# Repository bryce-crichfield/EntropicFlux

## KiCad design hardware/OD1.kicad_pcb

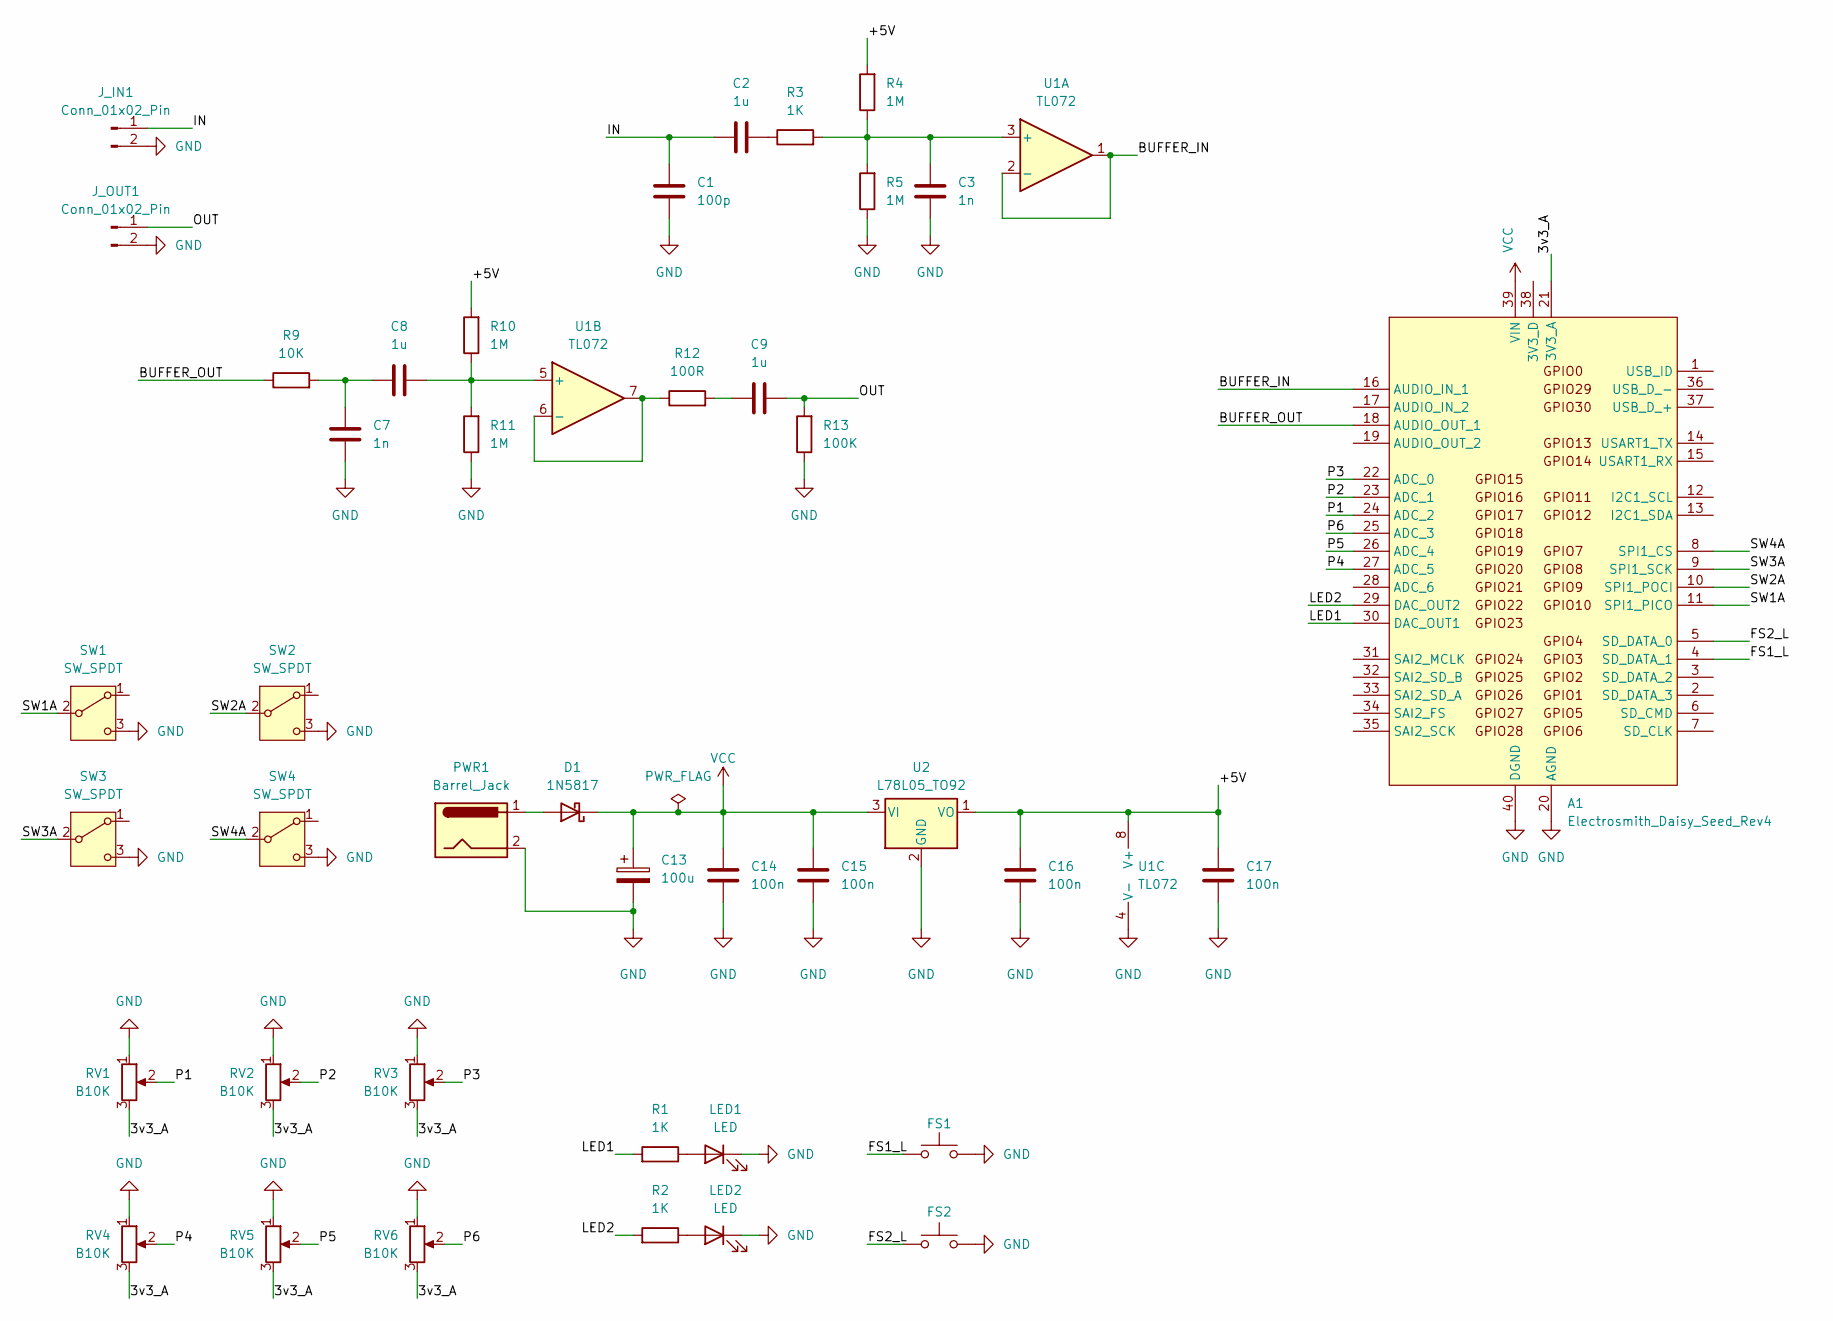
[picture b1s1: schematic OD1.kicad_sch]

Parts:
A1: Electrosmith_Daisy_Seed_Rev4; Electrosmith_Daisy_Seed
C1: 100p; C_Rect_L7.2mm_W2.5mm_P5.00mm_FKS2_FKP2_MKS2_MKP2
C2, C8, C9: 1u; C_Rect_L7.2mm_W2.5mm_P5.00mm_FKS2_FKP2_MKS2_MKP2
C3, C7: 1n; C_Rect_L7.2mm_W2.5mm_P5.00mm_FKS2_FKP2_MKS2_MKP2
C13: 100u; CP_Radial_D8.0mm_P3.50mm
C14, C15, C16, C17: 100n; C_Rect_L7.2mm_W2.5mm_P5.00mm_FKS2_FKP2_MKS2_MKP2
D1: 1N5817; D_DO-41_SOD81_P10.16mm_Horizontal
FS1, FS2: PinHeader_1x02_P2.54mm_Vertical
J_IN1: Conn_01x02_Pin; PinHeader_1x02_P2.54mm_Vertical
J_OUT1: Conn_01x02_Pin; PinHeader_1x02_P2.54mm_Vertical
LED1, LED2: LED; LED_D5.0mm
PWR1: Barrel_Jack; PinHeader_1x02_P2.54mm_Vertical
R1, R2, R3: 1K; R_Axial_DIN0207_L6.3mm_D2.5mm_P10.16mm_Horizontal
R4, R5, R10, R11: 1M; R_Axial_DIN0207_L6.3mm_D2.5mm_P10.16mm_Horizontal
R9: 10K; R_Axial_DIN0207_L6.3mm_D2.5mm_P10.16mm_Horizontal
R12: 100R; R_Axial_DIN0207_L6.3mm_D2.5mm_P10.16mm_Horizontal
R13: 100K; R_Axial_DIN0207_L6.3mm_D2.5mm_P10.16mm_Horizontal
RV1, RV2, RV3, RV4, RV5, RV6: B10K; Potentiometer_3Pin_Holes
SW1, SW2, SW3, SW4: SW_SPDT; Toggle_Switch_3Pin_Holes
U1: TL072; DIP-8_W7.62mm
U2: L78L05_TO92; TO-92_Inline

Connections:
/3v3_A: A1.21 (3V3_A), RV1.3, RV2.3, RV3.3, RV4.3, RV5.3, RV6.3
/+5V: C16.2, C17.2, R4.2, R10.2, U1.8 (V+), U2.1 (VO)
/BUFFER_IN: A1.16 (AUDIO_IN_1), U1.1, U1.2 (-)
/BUFFER_OUT: A1.18 (AUDIO_OUT_1), R9.1
/FS1_L: A1.4 (SD_DATA_1), FS1.1
/FS2_L: A1.5 (SD_DATA_0), FS2.1
/IN: C1.1, C2.1, J_IN1.1
/LED1: A1.30 (DAC_OUT1), R1.2
/LED2: A1.29 (DAC_OUT2), R2.2
/OUT: C9.2, J_OUT1.1, R13.2
/P1: A1.24 (ADC_2), RV1.2
/P2: A1.23 (ADC_1), RV2.2
/P3: A1.22 (ADC_0), RV3.2
/P4: A1.27 (ADC_5), RV4.2
/P5: A1.26 (ADC_4), RV5.2
/P6: A1.25 (ADC_3), RV6.2
/SW1A: A1.11 (SPI1_PICO), SW1.2 (B)
/SW2A: A1.10 (SPI1_POCI), SW2.2 (B)
/SW3A: A1.9 (SPI1_SCK), SW3.2 (B)
/SW4A: A1.8 (SPI1_CS), SW4.2 (B)
GND: A1.20 (AGND), A1.40 (DGND), C1.2, C3.2, C7.2, C13.2, C14.1, C15.1, C16.1, C17.1, FS1.2, FS2.2, J_IN1.2, J_OUT1.2, LED1.1 (K), LED2.1 (K), PWR1.2, R5.1, R11.1, R13.1, RV1.1, RV2.1, RV3.1, RV4.1, RV5.1, RV6.1, SW1.3 (C), SW2.3 (C), SW3.3 (C), SW4.3 (C), U1.4 (V-), U2.2 (GND)
unnamed: C2.2, R3.1
unnamed: C7.1, C8.1, R9.2
unnamed: C9.1, R12.2
unnamed: D1.2 (A), PWR1.1
unnamed: LED1.2 (A), R1.1
unnamed: LED2.2 (A), R2.1
unnamed: C3.1, R3.2, R4.1, R5.2, U1.3 (+)
unnamed: C8.2, R10.1, R11.2, U1.5 (+)
unnamed: R12.1, U1.6 (-), U1.7
VCC: A1.39 (VIN), C13.1, C14.2, C15.2, D1.1 (K), U2.3 (VI)

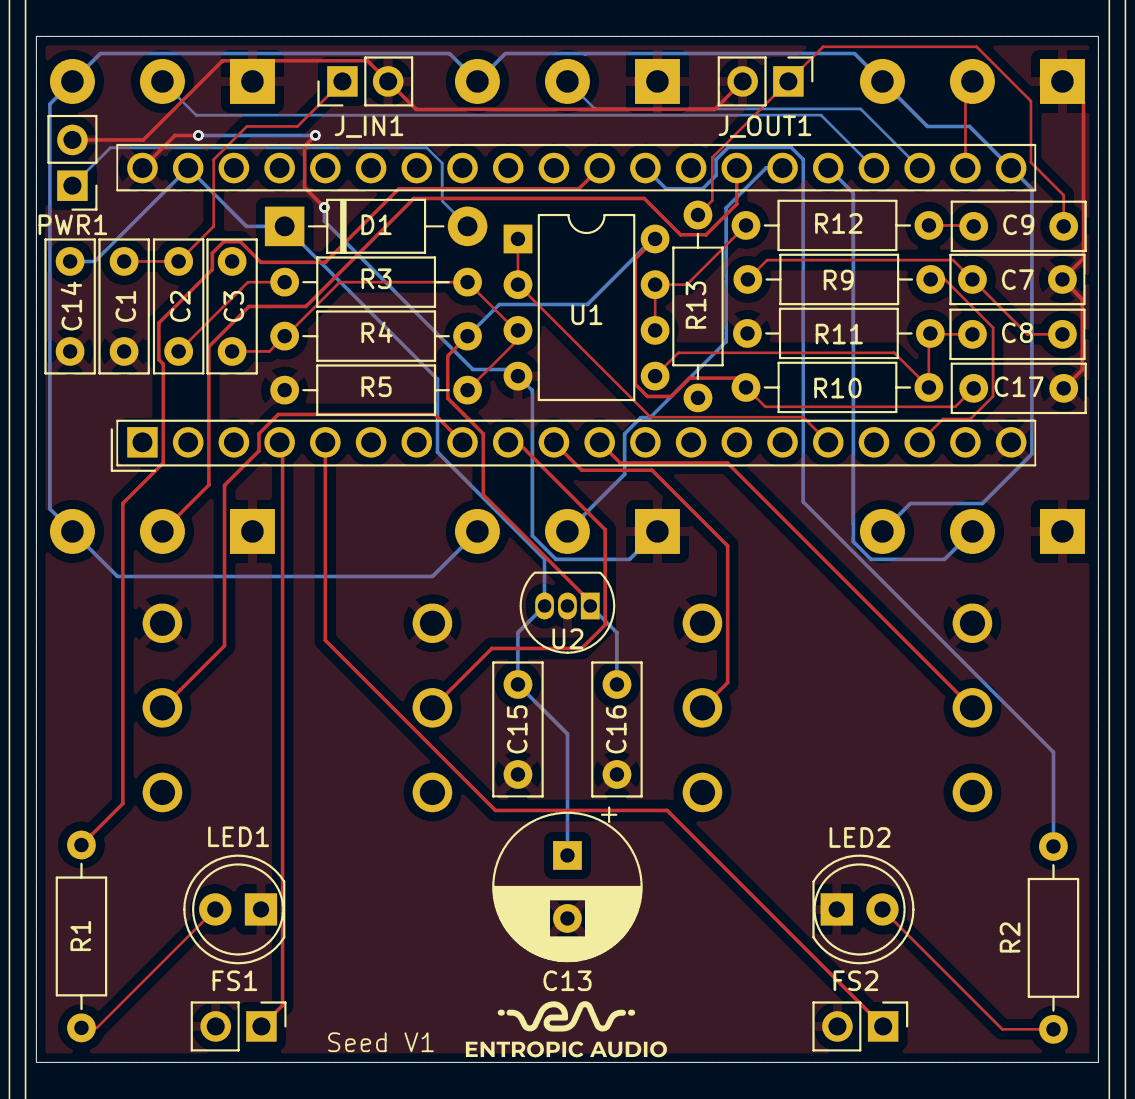
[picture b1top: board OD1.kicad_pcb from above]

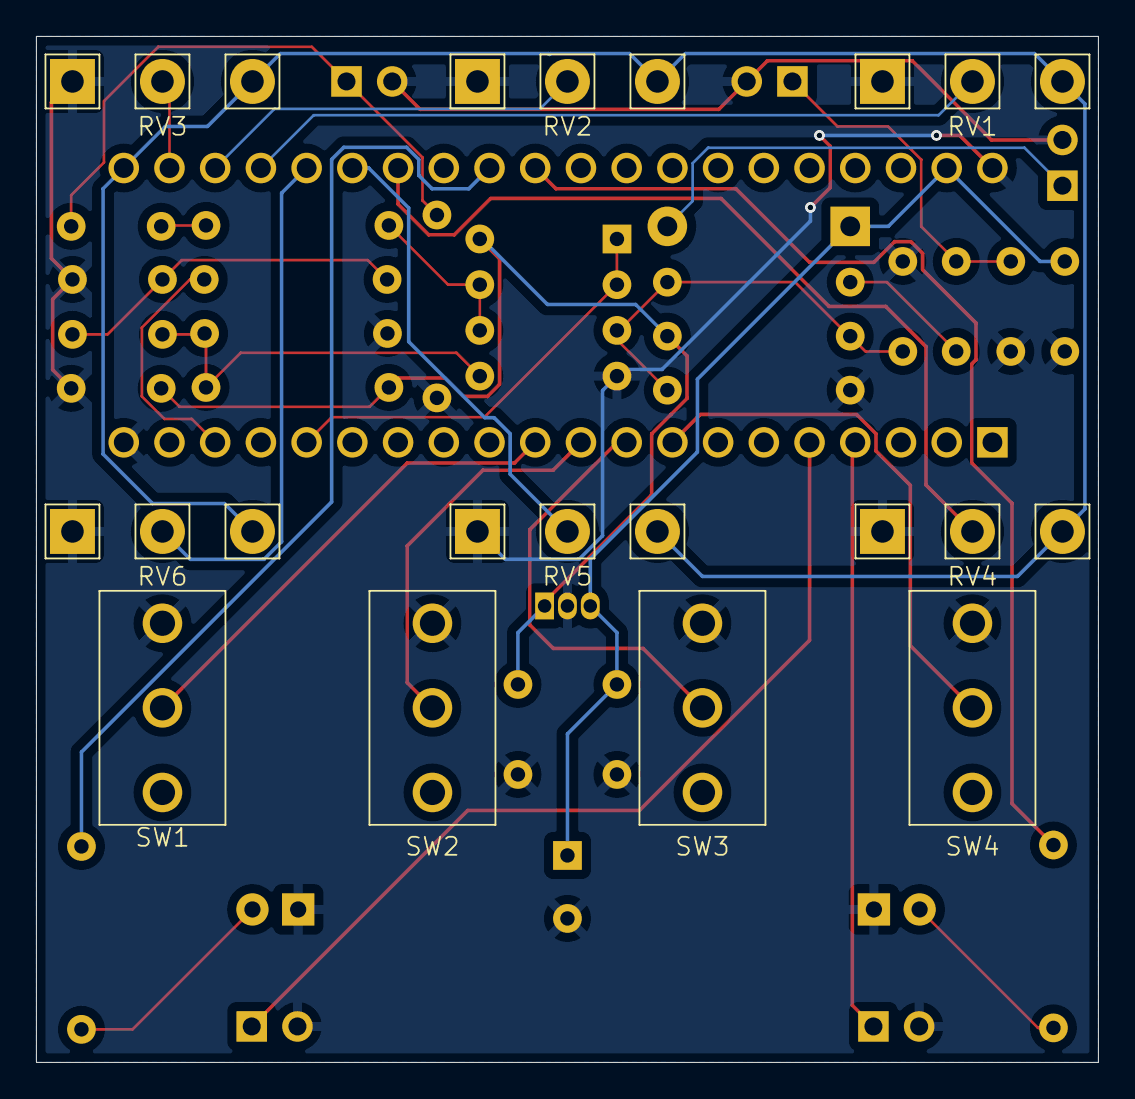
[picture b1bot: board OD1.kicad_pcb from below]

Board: 2 copper layers, 59.0 x 57.0 mm, 42 parts (10 on the bottom side), 31 nets.

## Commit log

2025-06-09 initializes the repo
2025-06-09 adds the hardware files
2025-06-10 adds DaisySY dependency as a submodule
2025-06-10 adds libDaisy dependency as a submodule
